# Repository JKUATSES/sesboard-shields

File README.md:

## Contribution Instructions
---

1. Fork the code sesboard shields repository provided.

2. Make a topic branch. In your github, keep the master branch clean. Pull all changes, make sure your repository is up to date.
```shell
cd [repo-name] e.g. cd research-docs
git pull origin main
```

3. Create a new branch as follows
```shell
git checkout -b <your_branch_name> main
```

4. See all branches created
```shell
$ git branch main <your_name>
```

5. Push the new branch to github
```shell
$ git push origin -u <your_branch_name>
```

6. Make changes to the fork provided.

7. Check the status of the repo
```shell
git status
```
8. Add your changed files
```shell
git add .
```
9. Commit your changes
```shell
git commit -m "Commit message"
```
10. Push your code changes
```shell
git push --set-upstream origin <your_name>
```
8. Make a [pull request](https://www.digitalocean.com/community/tutorials/how-to-create-a-pull-request-on-github) to the [Repo Name]

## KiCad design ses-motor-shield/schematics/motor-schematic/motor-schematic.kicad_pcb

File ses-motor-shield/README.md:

# SES-Board Motor Shield

---
The SES-Board Motor Shield features several outputs that can be useful to 
run motors for your projects needs. It features the following:
1. 2 servo motor control outputs
2. 4 DC motor control outputs
3. 1 stepper motor control output
4. External power supply
5. GPIO pins extension allowance
6. 3 LD293 Motor Driver ICs for high-current motor control
7. NEMA 17 stepper motor control 

The GPIO pins can be uses to connect to other sensors or outputs
you might want to control

# SES-Board Motor Shield Pin Assignments
The following table describes the pin assignment for each component
of the SES-Board motor shield:

| COMPONENT | PIN ON SESBOARD|
|-----------|---|
|**DC Motor 1**
|IN1|34|
|IN2|35|
|IN3|32|
|IN4|33|
|ENA|25|
|ENB|26|
|**DC Motor 2**| 
IN5|23|
|IN6|22|
|IN7|21|
|IN8|19|
|ENC|18|
|END|5|
|**Servo 1**
|SIG|17|
|Servo 2|
| SIG|16|
|**Stepper Motor**|
|A+|12|
|A-|13|
|B+|14|
|B-|15|

*** For ESP32, pins 34-39 cannot support PWM***

## Design 
### 1. Power supply
Power is derived from 12VDC supply. Because majority of motors run within this range,
this 12V is used to supply the motors with power. A 2-terminal block is used
to receive this 12V input. It then passes through a rectifier diode connected in forward bias 
to prevent reverse polarity damage. The diode drops 0.7V forward voltage.  
An LM317 voltage regulator is placed on the line for regulation. R1=240R and R2=2K. R1 and R2 ensure we get an output
of 12V regulated. Vout is given by this formula:
```c
Vout = 1.25(1 + R2/R1)
```

An NPN transistor (TIP3055), is connected to allow the shield to handle large current values when running.
A jumper is then placed at the collector of the transistor to allow for programming of the sesboard when using 
this motor shield.

****Make sure you cross-check your motor voltage range before using 12VDC***

<br>
Most servo motors operate under 6V of power. Fo us to supply this amount of voltage, we need to step down the 12V down to ~6V. We use an AMS1117-5V LDO regulator 
to provide us with ~5V which is enough for servo motors.   

<br>

During programming, we need to power the sesboard. We use AMS1117-3V3 LDO regulator for this task. It will provide
3V3 to the sesboard for optimal function.
There is a green LED to provide indication that there is power flowing in the circuit.

<hr>  

### 2. Driver ICs
We use the very common L293D motor driver ICs. The L293D motor driver can drive up to 

## Screenshots
### Top

### Bottom

### Left

# References
1. [https://lastminuteengineers.com/l293d-dc-motor-arduino-tutorial/](https://lastminuteengineers.com/l293d-dc-motor-arduino-tutorial/)
2. [https://lastminuteengineers.com/stepper-motor-l293d-arduino-tutorial/](https://lastminuteengineers.com/stepper-motor-l293d-arduino-tutorial/)
3. [https://randomnerdtutorials.com/esp32-pinout-reference-gpios/#:~:text=The%20ESP32%20LED%20PWM%20controller,can't%20generate%20PWM)] (https://randomnerdtutorials.com/esp32-pinout-reference-gpios/#:~:text=The%20ESP32%20LED%20PWM%20controller,can't%20generate%20PWM)

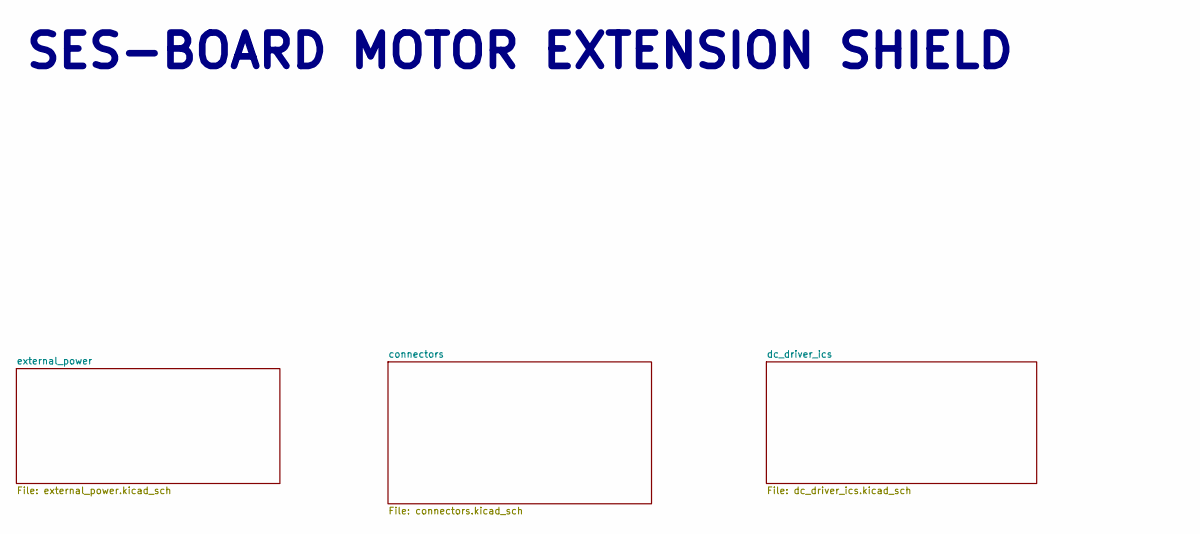
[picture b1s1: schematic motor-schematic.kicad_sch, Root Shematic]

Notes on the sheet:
SES-BOARD MOTOR EXTENSION SHIELD

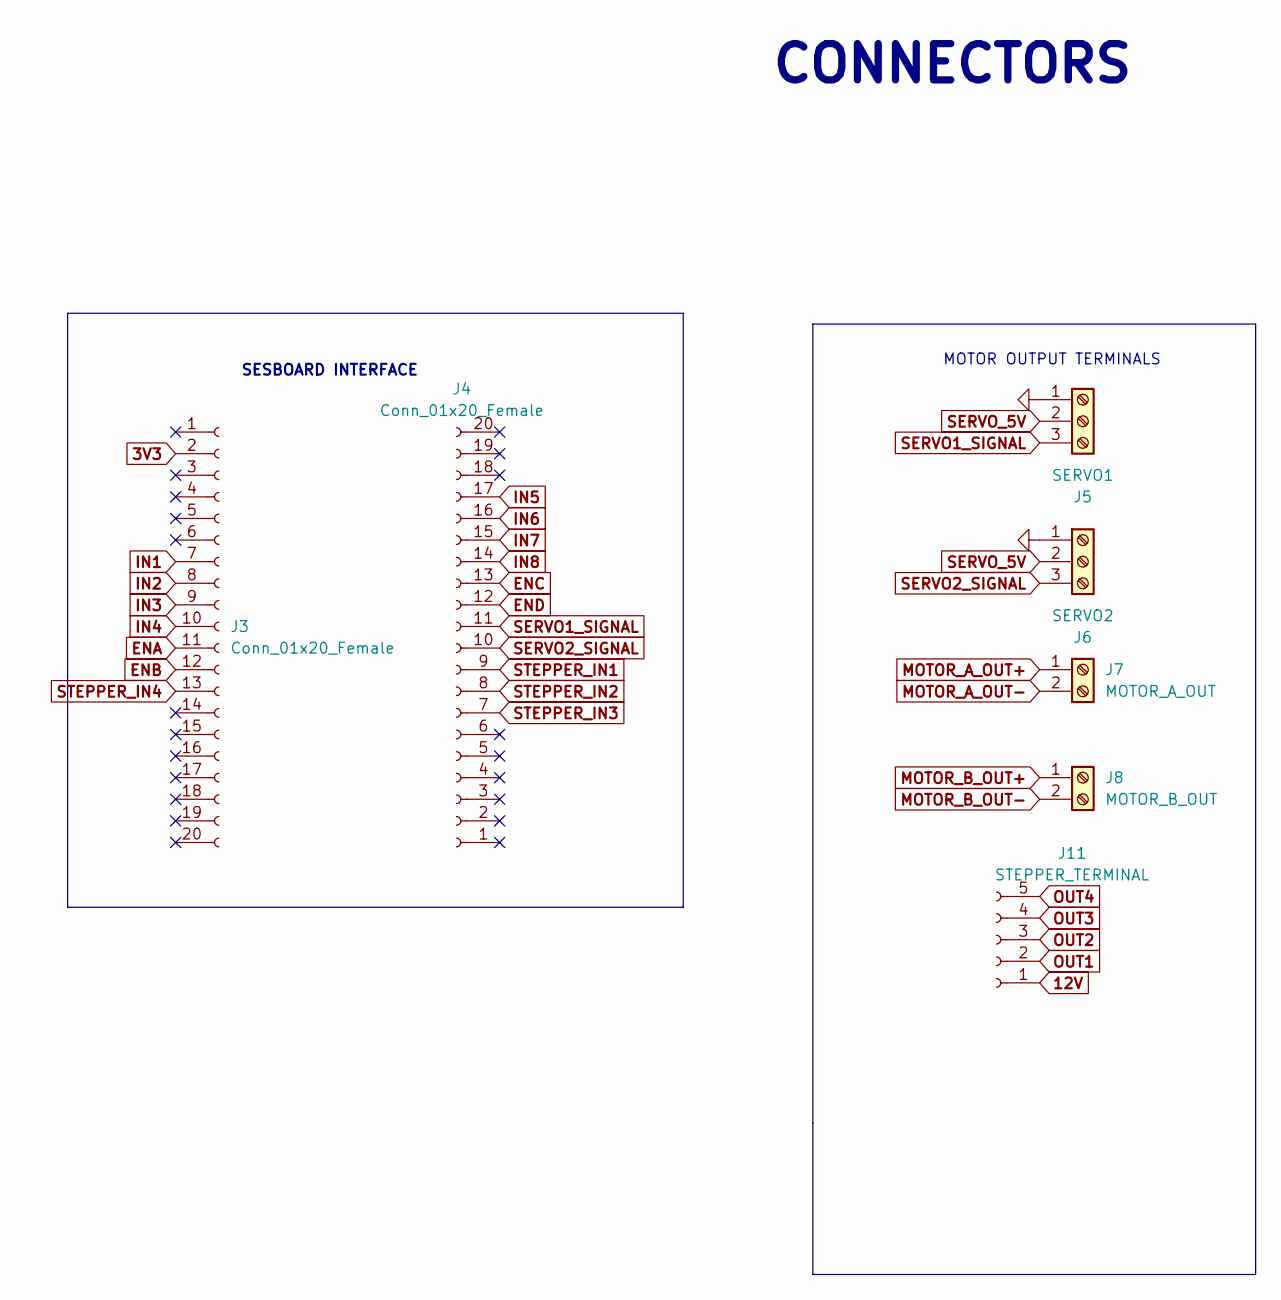
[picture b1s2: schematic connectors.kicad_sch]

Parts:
J3, J4: Conn_01x20_Female; PinHeader_1x20_P2.54mm_Vertical
J5: SERVO1; PinHeader_1x03_P2.54mm_Vertical
J6: SERVO2; PinHeader_1x03_P2.54mm_Vertical
J7: MOTOR_A_OUT; TerminalBlock_Phoenix_MKDS-1,5-2_1x02_P5.00mm_Horizontal
J8: MOTOR_B_OUT; TerminalBlock_Phoenix_MKDS-1,5-2_1x02_P5.00mm_Horizontal
J11: STEPPER_TERMINAL; PinHeader_1x05_P2.54mm_Vertical

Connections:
3V3: J3.2
12V: J11.1; also elsewhere on the board
ENA: J3.11; also elsewhere on the board
ENB: J3.12; also elsewhere on the board
ENC: J4.13; also elsewhere on the board
END: J4.12; also elsewhere on the board
GND: J5.1, J6.1; also elsewhere on the board
IN1: J3.7; also elsewhere on the board
IN2: J3.8; also elsewhere on the board
IN3: J3.9; also elsewhere on the board
IN4: J3.10; also elsewhere on the board
IN5: J4.17; also elsewhere on the board
IN6: J4.16; also elsewhere on the board
IN7: J4.15; also elsewhere on the board
IN8: J4.14; also elsewhere on the board
MOTOR_A_OUT+: J7.1; also elsewhere on the board
MOTOR_A_OUT-: J7.2; also elsewhere on the board
MOTOR_B_OUT+: J8.1; also elsewhere on the board
MOTOR_B_OUT-: J8.2; also elsewhere on the board
OUT1: J11.2; also elsewhere on the board
OUT2: J11.3; also elsewhere on the board
OUT3: J11.4; also elsewhere on the board
OUT4: J11.5; also elsewhere on the board
SERVO1_SIGNAL: J4.11, J5.3
SERVO2_SIGNAL: J4.10, J6.3
SERVO_5V: J5.2, J6.2; also elsewhere on the board
STEPPER_IN1: J4.9; also elsewhere on the board
STEPPER_IN2: J4.8; also elsewhere on the board
STEPPER_IN3: J4.7; also elsewhere on the board
STEPPER_IN4: J3.13; also elsewhere on the board

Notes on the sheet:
MOTOR OUTPUT TERMINALS
SESBOARD INTERFACE
CONNECTORS

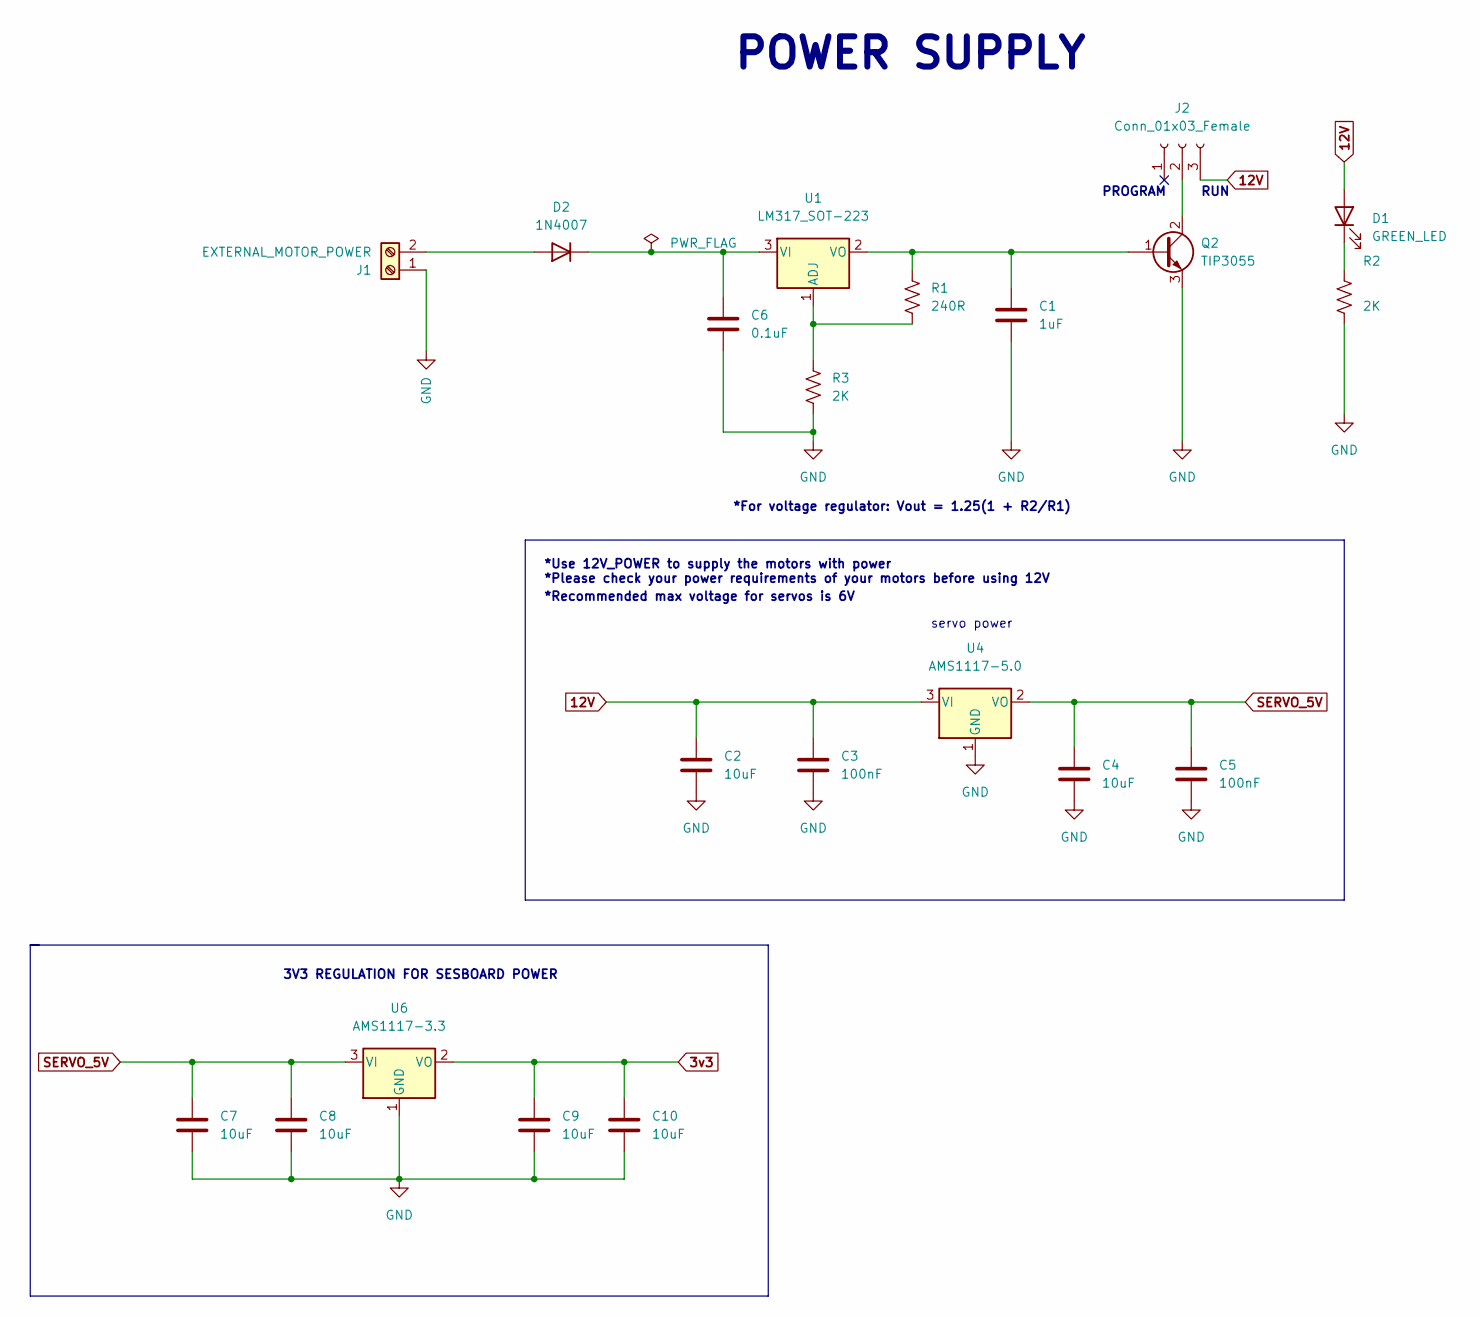
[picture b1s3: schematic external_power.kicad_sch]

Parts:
C1: 1uF; C_0603_1608Metric
C2, C4, C7, C8, C9, C10: 10uF; C_0603_1608Metric
C3: 100nF; C_0603_1608Metric
C5: 100nF; C_0603_1608Metric_Pad1.08x0.95mm_HandSolder
C6: 0.1uF; C_0603_1608Metric
D1: GREEN_LED; LED_0603_1608Metric
D2: 1N4007; D_DO-41_SOD81_P10.16mm_Horizontal
J1: EXTERNAL_MOTOR_POWER; TerminalBlock_Phoenix_MKDS-1,5-2_1x02_P5.00mm_Horizontal
J2: Conn_01x03_Female; PinHeader_1x03_P2.54mm_Vertical
Q2: TIP3055; TO-220-3_Vertical
R1: 240R; R_0603_1608Metric
R2, R3: 2K; R_0603_1608Metric
U1: LM317_SOT-223; SOT-223-3_TabPin2
U4: AMS1117-5.0; SOT-223-3_TabPin2
U6: AMS1117-3.3; SOT-223-3_TabPin2

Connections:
3v3: C9.1, C10.1, U6.2 (VO)
12V: C2.1, C3.1, D1.2 (A), J2.3, U4.3 (VI); also elsewhere on the board
GND: C1.2, C2.2, C3.2, C4.2, C5.2, C6.2, C7.2, C8.2, C9.2, C10.2, J1.1, Q2.3 (E), R2.2, R3.2, U4.1 (GND), U6.1 (GND); also elsewhere on the board
unnamed: C1.1, Q2.1 (B), R1.1, U1.2 (VO)
unnamed: C6.1, D2.1 (K), U1.3 (VI)
unnamed: D1.1 (K), R2.1
unnamed: D2.2 (A), J1.2
unnamed: J2.2, Q2.2 (C)
unnamed: R1.2, R3.1, U1.1 (ADJ)
SERVO_5V: C4.1, C5.1, C7.1, C8.1, U4.2 (VO), U6.3 (VI); also elsewhere on the board

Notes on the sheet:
*Use 12V_POWER to supply the motors with power *Please check your power requirements of your motors before using 12V
*Recommended max voltage for servos is 6V
POWER SUPPLY
RUN
*For voltage regulator: Vout = 1.25(1 + R2/R1)
3V3 REGULATION FOR SESBOARD POWER
PROGRAM
servo power

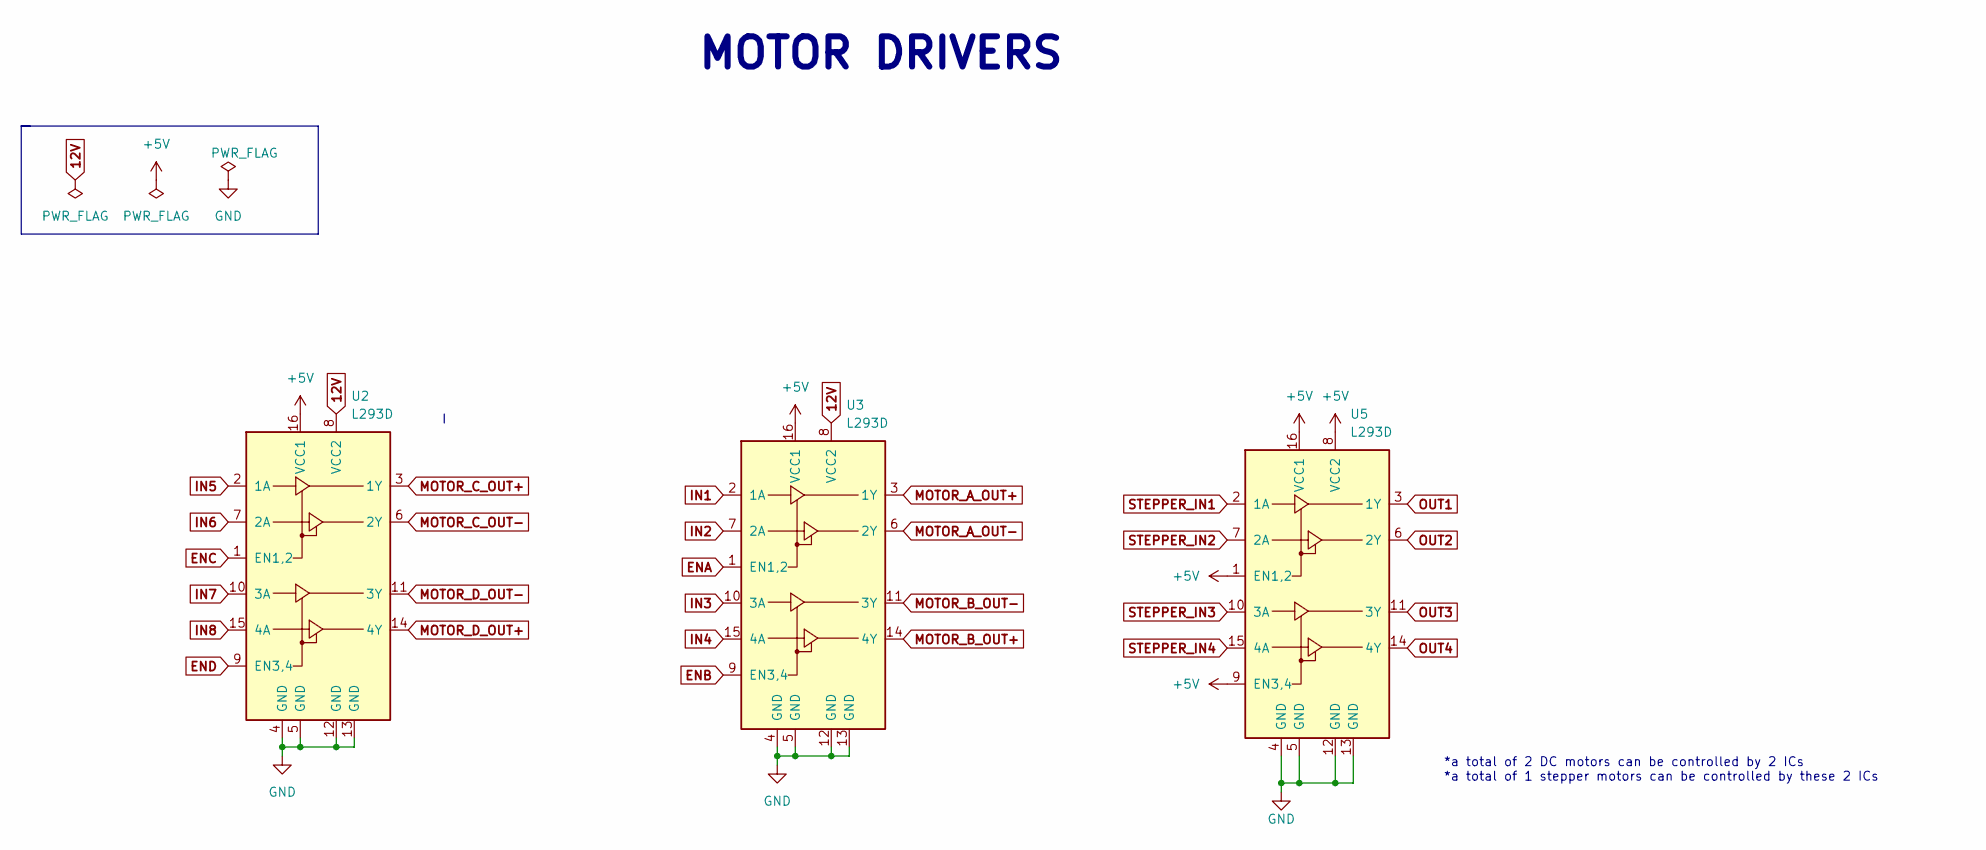
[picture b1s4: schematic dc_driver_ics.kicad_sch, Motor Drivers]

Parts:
U2, U3, U5: L293D; DIP-16_W7.62mm

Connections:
12V: U2.8 (VCC2), U3.8 (VCC2); also elsewhere on the board
+5V: U2.16 (VCC1), U3.16 (VCC1), U5.1 (EN1,2), U5.8 (VCC2), U5.9 (EN3,4), U5.16 (VCC1)
ENA: U3.1 (EN1,2); also elsewhere on the board
ENB: U3.9 (EN3,4); also elsewhere on the board
ENC: U2.1 (EN1,2); also elsewhere on the board
END: U2.9 (EN3,4); also elsewhere on the board
GND: U2.4 (GND), U2.5 (GND), U2.12 (GND), U2.13 (GND), U3.4 (GND), U3.5 (GND), U3.12 (GND), U3.13 (GND), U5.4 (GND), U5.5 (GND), U5.12 (GND), U5.13 (GND); also elsewhere on the board
IN1: U3.2 (1A); also elsewhere on the board
IN2: U3.7 (2A); also elsewhere on the board
IN3: U3.10 (3A); also elsewhere on the board
IN4: U3.15 (4A); also elsewhere on the board
IN5: U2.2 (1A); also elsewhere on the board
IN6: U2.7 (2A); also elsewhere on the board
IN7: U2.10 (3A); also elsewhere on the board
IN8: U2.15 (4A); also elsewhere on the board
MOTOR_A_OUT+: U3.3 (1Y); also elsewhere on the board
MOTOR_A_OUT-: U3.6 (2Y); also elsewhere on the board
MOTOR_B_OUT+: U3.14 (4Y); also elsewhere on the board
MOTOR_B_OUT-: U3.11 (3Y); also elsewhere on the board
MOTOR_C_OUT+: U2.3 (1Y)
MOTOR_C_OUT-: U2.6 (2Y)
MOTOR_D_OUT+: U2.14 (4Y)
MOTOR_D_OUT-: U2.11 (3Y)
OUT1: U5.3 (1Y); also elsewhere on the board
OUT2: U5.6 (2Y); also elsewhere on the board
OUT3: U5.11 (3Y); also elsewhere on the board
OUT4: U5.14 (4Y); also elsewhere on the board
STEPPER_IN1: U5.2 (1A); also elsewhere on the board
STEPPER_IN2: U5.7 (2A); also elsewhere on the board
STEPPER_IN3: U5.10 (3A); also elsewhere on the board
STEPPER_IN4: U5.15 (4A); also elsewhere on the board

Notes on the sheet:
*a total of 2 DC motors can be controlled by 2 ICs *a total of 1 stepper motors can be controlled by these 2 ICs
MOTOR DRIVERS

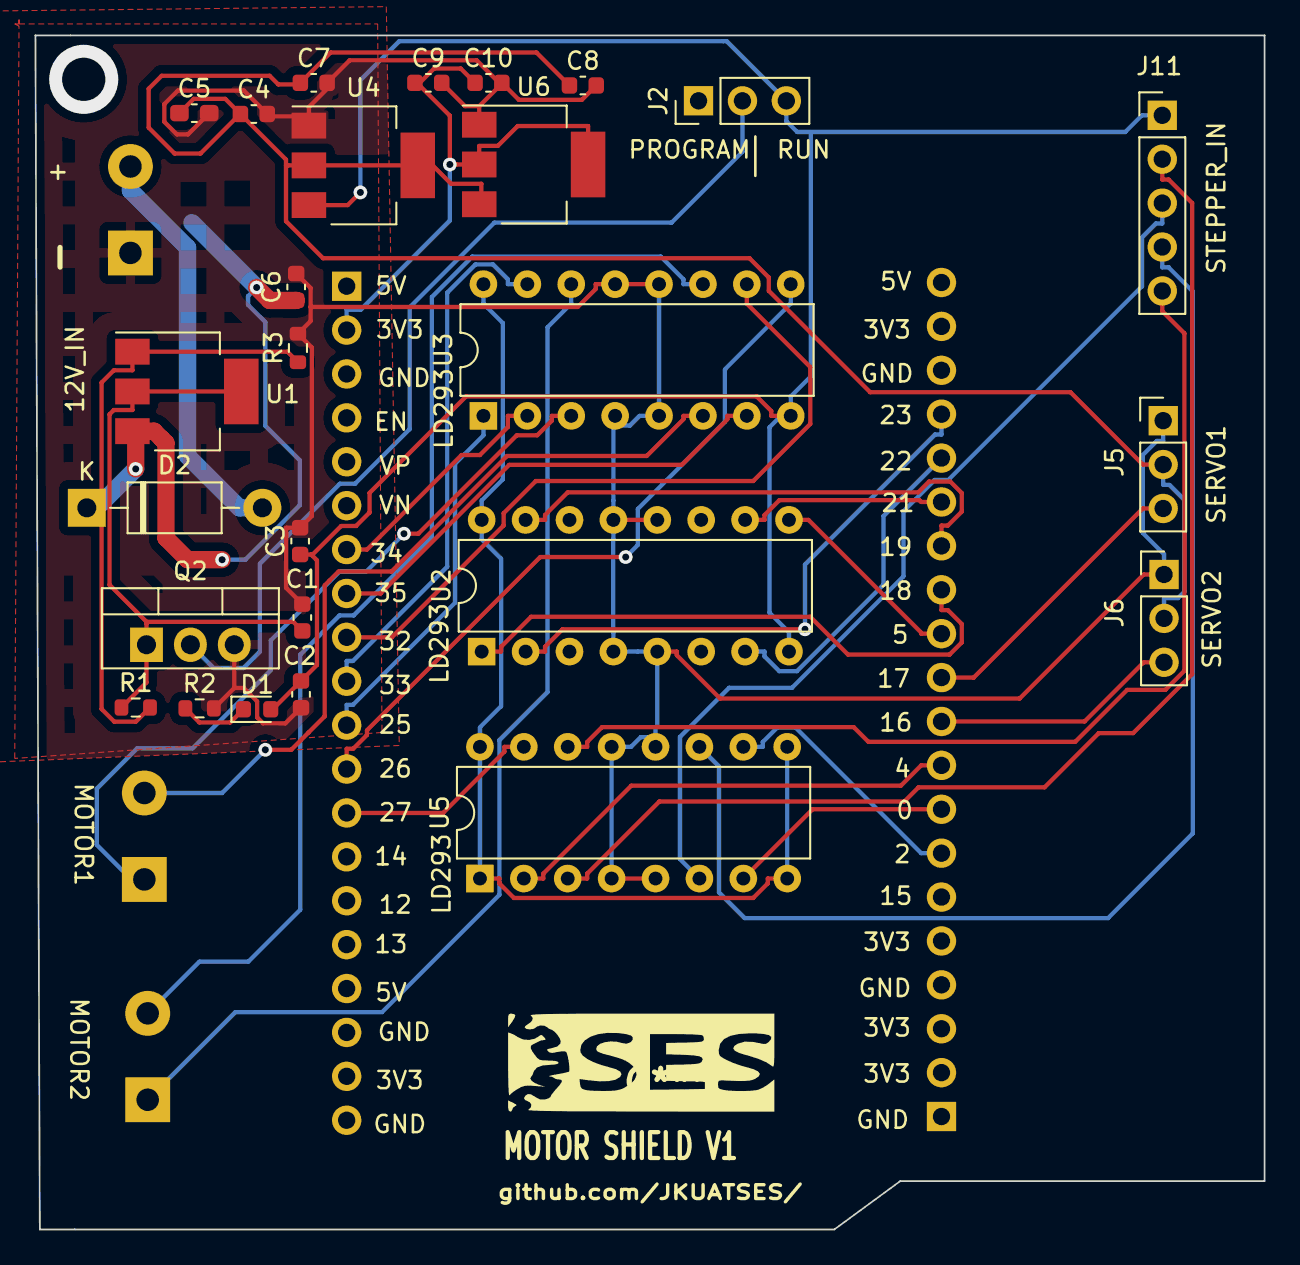
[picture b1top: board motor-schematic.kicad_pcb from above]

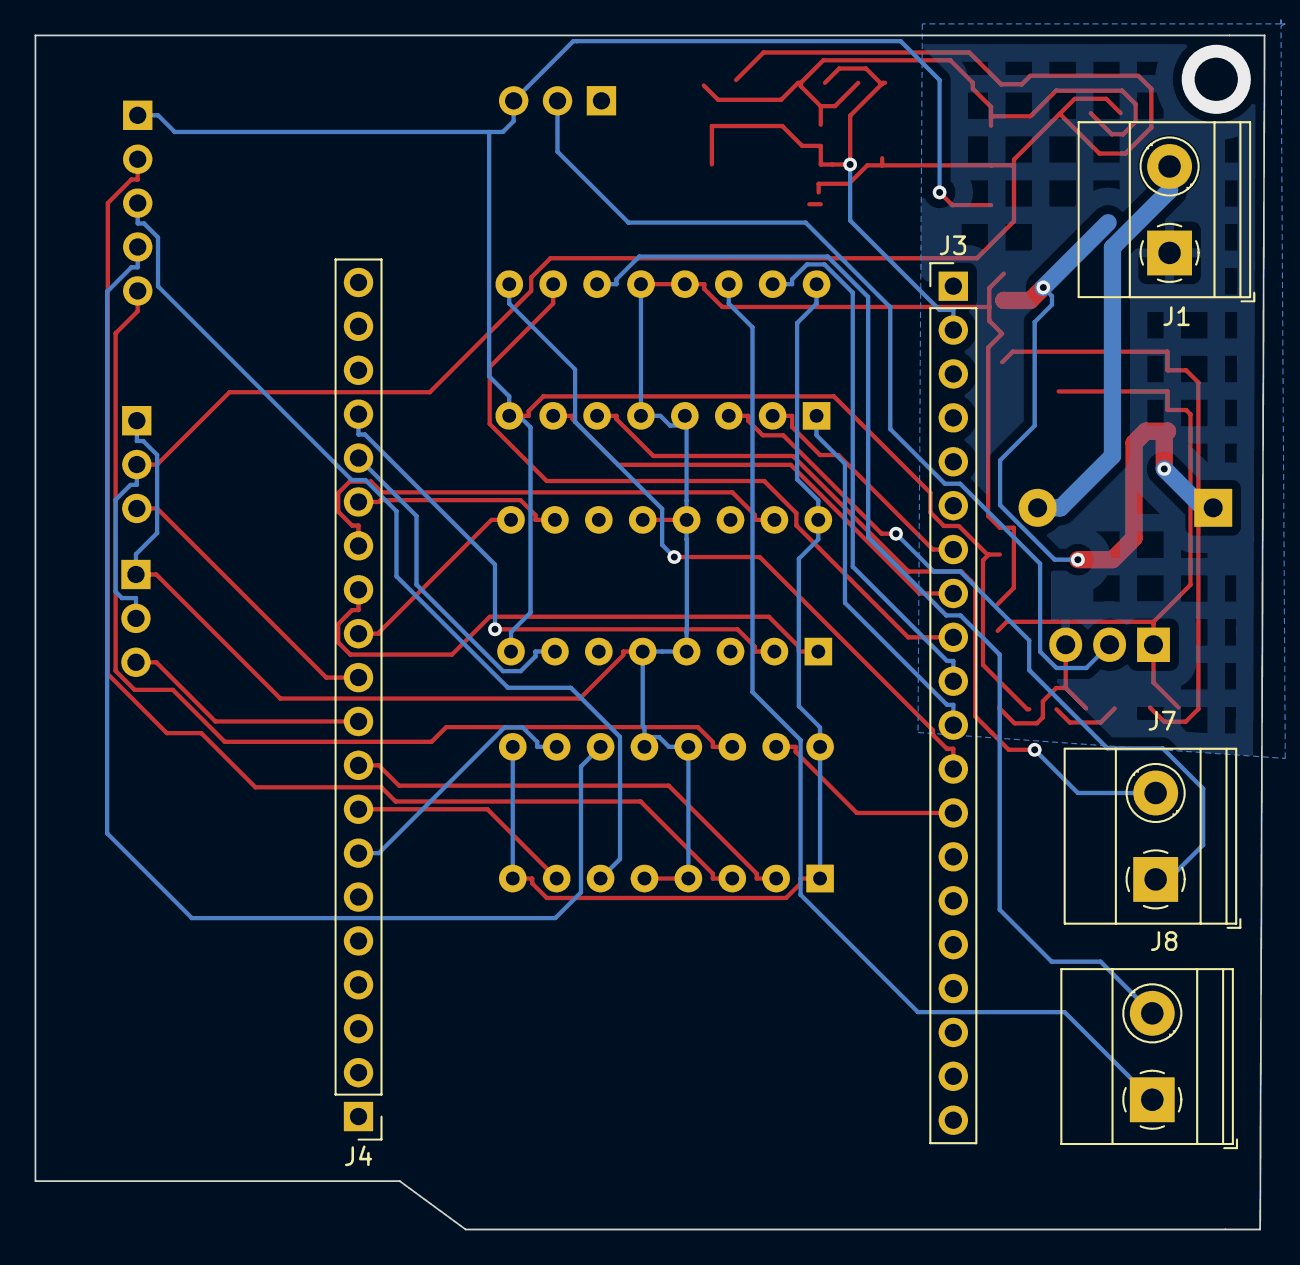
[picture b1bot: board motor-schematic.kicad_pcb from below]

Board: 2 copper layers, 71.1 x 69.1 mm, 31 parts (5 on the bottom side), 37 nets.

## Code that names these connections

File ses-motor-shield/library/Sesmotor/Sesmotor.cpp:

/*
 * Control dc motors using L298N Motor driver
 *
 * Author: Edwin Mwiti Maingi <emwiti658@gmail.com>
 * Date: September 12, 2022
 */

#include "Sesmotor.h
#include <Arduino.h>

//

Sesmotor::Sesmotor(int in1, int in2, int in3, int in4, int ena, int enb, int pwm_channel = 0, int pwm_frequency = 5000, int pwm_resolution = 8 ){

    /*
     * initialize dc motor
     */

    Serial.println("DC motor initialized!");

    _in1 = in1;
    _in2 = in2;
    _in3 = in3;
    _in4 = in4;
    _ena = ena;
    _enb = enb;
    _channel = pwm_channel;
    _frequency = pwm_frequency;
    _resolution = pwm_resolution;

    // set the PWM channel for ESP32
    // we  need to set up the frequency, channel and resolution parameters
    ledcSetup(pwm_channel, pwm_frequency, pwm_resolution);
    ledcAttachPin(ena, pwm_channel);
    ledcAttachPin(enb, pwm_channel);

    // set parameter pins as output
    pinMode(in1, OUTPUT);
    pinMode(in2, OUTPUT);
    pinMode(in3, OUTPUT);
    pinMode(in4, OUTPUT);
    pinMode(ena, OUTPUT);
    pinMode(enb, OUTPUT);
}

Sesmotor::Sesmotor(int servo_pin){
    /*
     * initialize servo motor
     */

    _servo_pin = servo_pin;

}

Sesmotor::Sesmotor(int steps_per_revolution, int in1, int in2, int in3, int in4) {
    /*
        Initialize the stepper motor library using the given pins
       
    */

    //_steps_per_revolution = steps_per_revolution;

    //_stepper_in1 = in1; // assign pins to private variables
    //_stepper_in2 = in2;
    //_stepper_in3 = in3;
    //_stepper_in4 = in4;

    // todo:test this method

    
}

/*
 * -----------------------Servo motor functions----------------------------------
 */

void Sesmotor::attachPin() {
    /*
     * attach servo object to pin
     */

    // Serial.println("Pin attached");
    this->attach(_servo_pin);  // use given pin as servo motor 
}

void Sesmotor::writeAngle(int angle){
    /*
     * set the servo to the given angle
     */
    this->write(angle);
    

}
/*
 * -----------------------End of Servo motor functions----------------------------------
 */


/*
 * ---------------------------------DC motor functions-----------------------------------
 */
 void Sesmotor::on(int speed){
    /*
     * Turn the motor on by writing
     * in1 = HIGH
     * in2 = LOW
     * in3 = HIGH
     * in4 = LOW
     */

    // write speed to motor
    ledcWrite(_ena, speed)
    ledcWrite(_enb, speed)

    digitalWrite(_in1, 1);
    digitalWrite(_in2, 0);
    digitalWrite(_in3, 1);
    digitalWrite(_in4, 0);

}

void Sesmotor::off(){
    /*
     * Turn the motor on by writing
     * in1 = HIGH
     * in2 = LOW
     * in3 = HIGH
     * in4 = LOW
     */

    digitalWrite(in1, 0);
    digitalWrite(in2, 0);
    digitalWrite(in3, 0);
    digitalWrite(in4, 0);

}

void Sesmotor::forward() {
    /*
     * Move the motor in the forward direction
     * This function is for avr boards
     */
    digitalWrite(in1, 1);
    digitalWrite(in2, 0);
    digitalWrite(in3, 1);
    digitalWrite(in4, 0);
}

void Sesmotor::reverse() {
    /*
     * Move the motor in the backward direction
     */
    digitalWrite(in1, 0);
    digitalWrite(in2, 1);
    digitalWrite(in3, 0);
    digitalWrite(in4, 1);
}

void Sesmotor::turnLeft() {
    /*
     * Move the motor in the left direction
     * Turn off the left motor and turn on the right motor
     */
    digitalWrite(in1, 0);
    digitalWrite(in2, 1);
    digitalWrite(in3, 0);
    digitalWrite(in4, 0);
}

void Sesmotor::turnRight() {
    /*
     * Move the motor in the right direction
     * Turn off the left motor and turn on the right motor
     */
    digitalWrite(in1, 0);
    digitalWrite(in2, 0);
    digitalWrite(in3, 0);
    digitalWrite(in4, 1);
}

/*
 * -----------------------------End of DC motor functions-------------------------
 */

/*
* ------------------------------- Stepper motor functions --------------------------
* These functions control the 28BYJ-48 Stepper motor
* 
*/

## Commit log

2022-05-26 added power supply for motor shield
2022-05-30 added servo power supply
2022-05-30 added output terminals
2022-06-01 added pin assignments
2022-06-01 performed ERC
2022-06-03 added global labels for motor drivers
2022-06-03 added stepper connector
2022-06-03 added power toggle
2022-06-11 moved tall components to bottom for stacking ability
2022-06-11 added view image
2022-06-11 initialized library
2022-06-15 added libary implementation
2022-06-15 Code cleanup
2022-09-05 added debug and test functions
2022-09-12 created: motor functions
2022-09-12 added initialization to close #5
2022-09-12 folder restructure
2022-09-13 finished board
2022-09-13 added shield documentation
2022-09-15 created function overloading for servo
2022-09-15 added servo sweep
2022-09-15 Changed "_inx" to Array
2022-09-16 Updated "_inx" to Array
2022-10-03 added: stepper motor examples
2022-10-03 created technical specs for ses-mp3 shield
2022-10-03 added specifications
